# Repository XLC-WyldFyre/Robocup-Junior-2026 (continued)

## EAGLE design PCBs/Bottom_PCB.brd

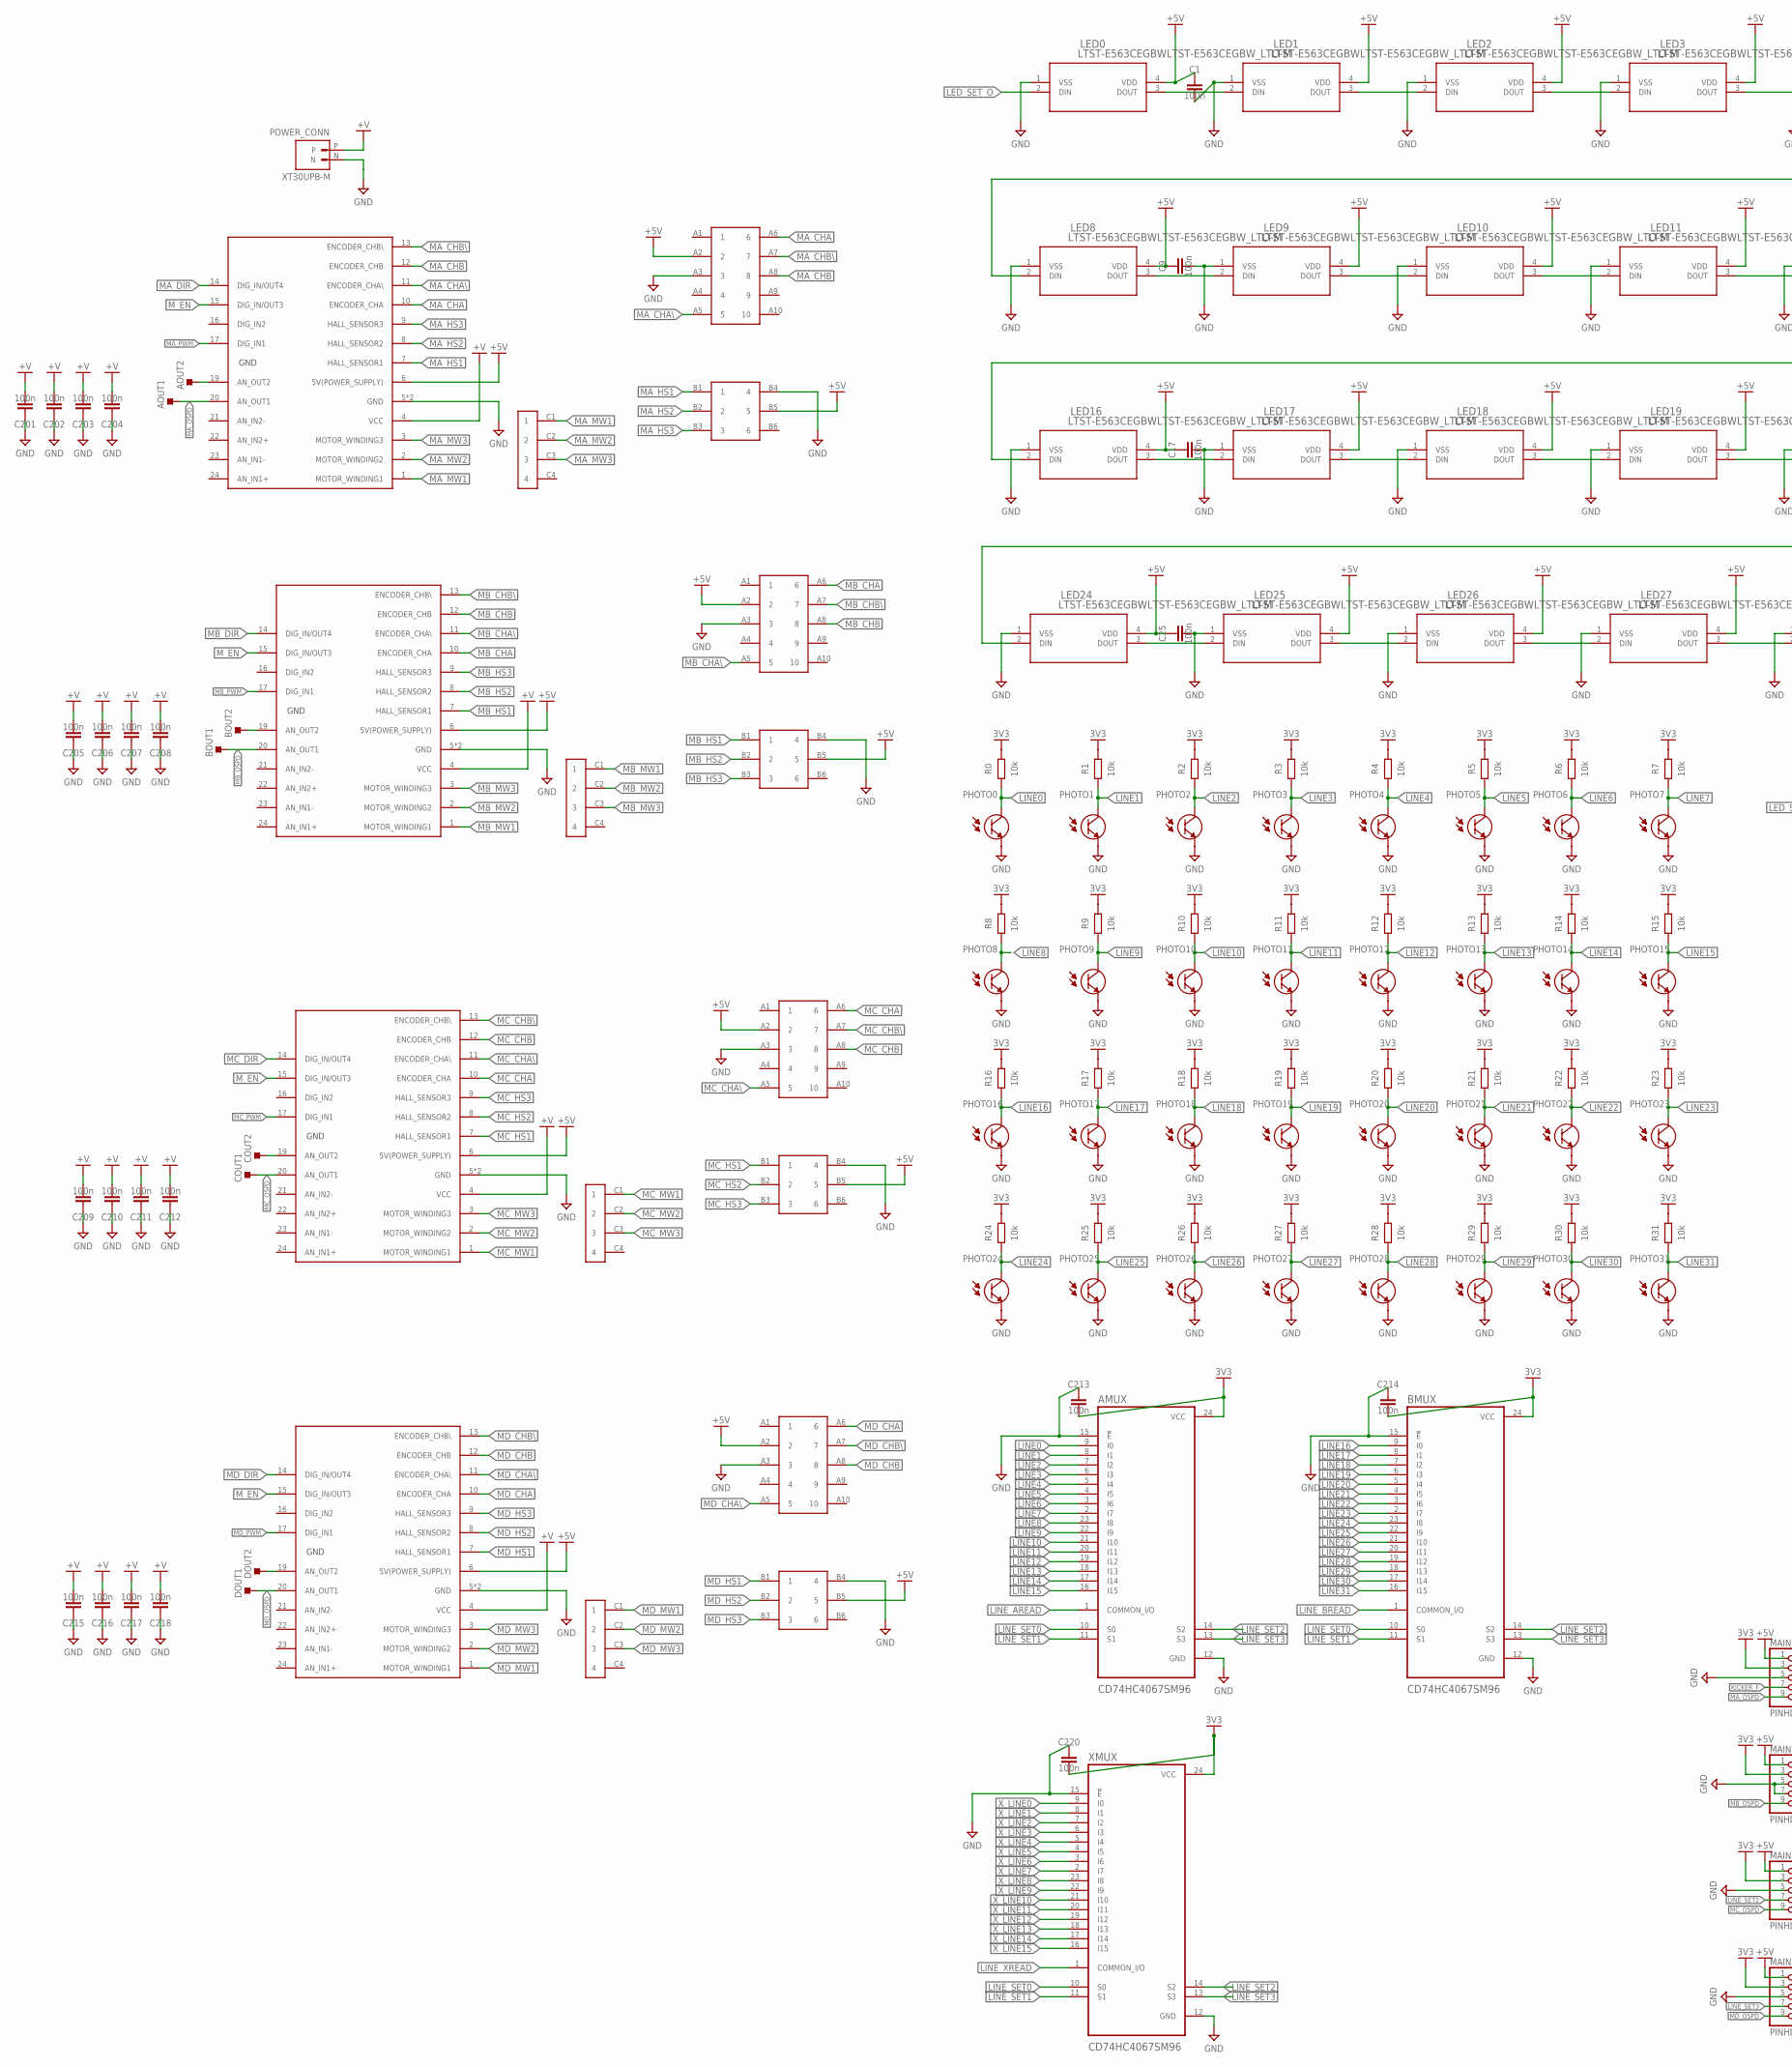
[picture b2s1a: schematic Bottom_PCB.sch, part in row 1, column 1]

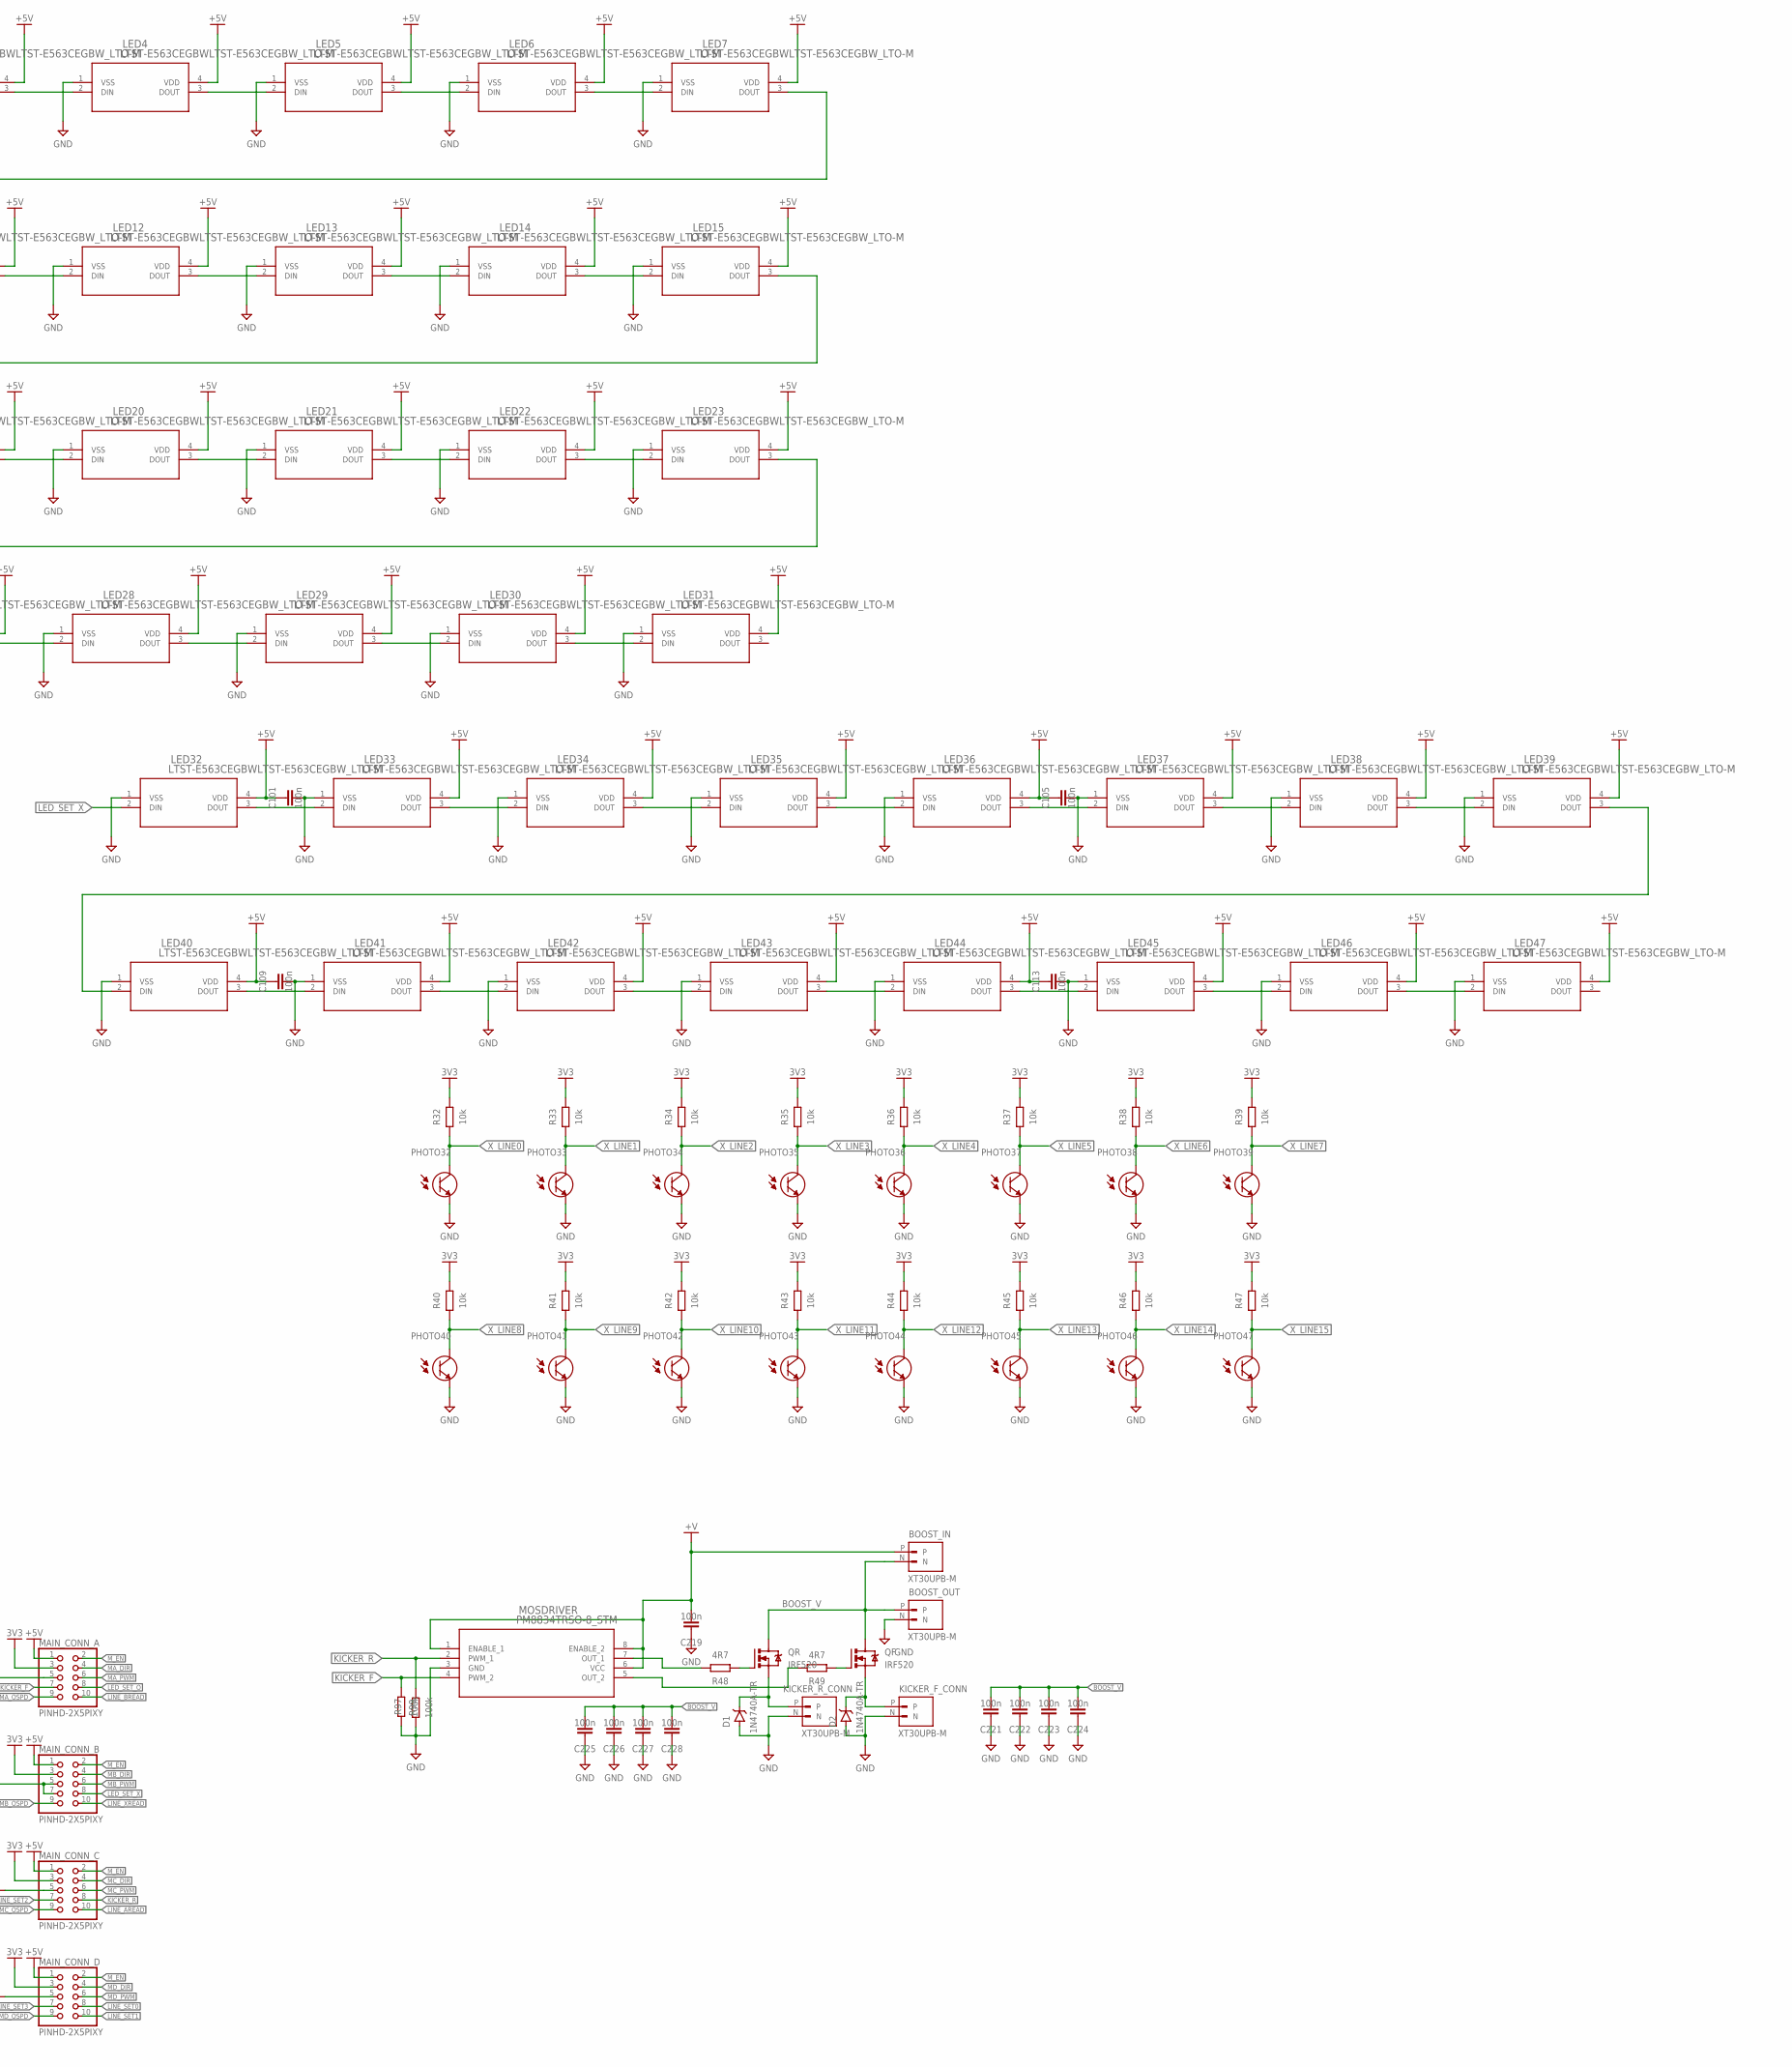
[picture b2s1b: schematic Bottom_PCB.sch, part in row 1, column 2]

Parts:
AENC: PIN2.54-2X5
AHAL: MX-44914-0601
AMD: ESCON24/224/2; ESCON24/2
AMUX: CD74HC4067SM96; SOP65P780X200-24N
AMW: MX5566
AOUT1, AOUT2: TESTPOINT_TPS-PAD-036; TESTPOINT_PAD-036
BENC: PIN2.54-2X5
BHAL: MX-44914-0601
BMD: ESCON24/224/2; ESCON24/2
BMUX: CD74HC4067SM96; SOP65P780X200-24N
BMW: MX5566
BOOST_IN: XT30UPB-M; AMASS_XT30UPB-M
BOOST_OUT: XT30UPB-M; AMASS_XT30UPB-M
BOUT1, BOUT2: TESTPOINT_TPS-PAD-036; TESTPOINT_PAD-036
C1, C9, C17, C25, C101, C105, C109, C113, C201, C202, C203, C204, C205, C206, C207, C208, C209, C210, C211, C212, C213, C214, C215, C216, C217, C218, C219, C220, C221, C222, C223, C224, C225, C226, C227, C228: 100n; CAPC2012X110
CENC: PIN2.54-2X5
CHAL: MX-44914-0601
CMD: ESCON24/224/2; ESCON24/2
CMW: MX5566
COUT1, COUT2: TESTPOINT_TPS-PAD-036; TESTPOINT_PAD-036
D1, D2: 1N4740A-TR; DO-41
DENC: PIN2.54-2X5
DHAL: MX-44914-0601
DMD: ESCON24/224/2; ESCON24/2
DMW: MX5566
DOUT1, DOUT2: TESTPOINT_TPS-PAD-036; TESTPOINT_PAD-036
KICKER_F_CONN: XT30UPB-M; AMASS_XT30UPB-M
KICKER_R_CONN: XT30UPB-M; AMASS_XT30UPB-M
LED0, LED1, LED2, LED3, LED4, LED5, LED6, LED7, LED8, LED9, LED10, LED11, LED12, LED13, LED14, LED15, LED16, LED17, LED18, LED19, LED20, LED21, LED22, LED23, LED24, LED25, LED26, LED27, LED28, LED29, LED30, LED31, LED32, LED33, LED34, LED35, LED36, LED37, LED38, LED39, LED40, LED41, LED42, LED43, LED44, LED45, LED46, LED47: LTST-E563CEGBWLTST-E563CEGBW_LTO-M; LTST-E563CEGBW_LTO-M
MAIN_CONN_A: PINHD-2X5PIXY; 2X05
MAIN_CONN_B: PINHD-2X5PIXY; 2X05
MAIN_CONN_C: PINHD-2X5PIXY; 2X05
MAIN_CONN_D: PINHD-2X5PIXY; 2X05
MOSDRIVER: PM8834TRSO-8_STM; SO-8_STM
PHOTO0, PHOTO1, PHOTO2, PHOTO3, PHOTO4, PHOTO5, PHOTO6, PHOTO7, PHOTO8, PHOTO9, PHOTO10, PHOTO11, PHOTO12, PHOTO13, PHOTO14, PHOTO15, PHOTO16, PHOTO17, PHOTO18, PHOTO19, PHOTO20, PHOTO21, PHOTO22, PHOTO23, PHOTO24, PHOTO25, PHOTO26, PHOTO27, PHOTO28, PHOTO29, PHOTO30, PHOTO31, PHOTO32, PHOTO33, PHOTO34, PHOTO35, PHOTO36, PHOTO37, PHOTO38, PHOTO39, PHOTO40, PHOTO41, PHOTO42, PHOTO43, PHOTO44, PHOTO45, PHOTO46, PHOTO47: RPM-075PTT86TRANS_RPM-075P_ROM; TRANS_RPM-075P_ROM
POWER_CONN: XT30UPB-M; AMASS_XT30UPB-M
QF: IRF520; TO220BV
QR: IRF520; TO220BV
R0, R1, R2, R3, R4, R5, R6, R7, R8, R9, R10, R11, R12, R13, R14, R15, R16, R17, R18, R19, R20, R21, R22, R23, R24, R25, R26, R27, R28, R29, R30, R31, R32, R33, R34, R35, R36, R37, R38, R39, R40, R41, R42, R43, R44, R45, R46, R47: 10k; RESC2012X65
R48, R49: 4R7; RESC2012X65
R97, R98: 100k; RESC2012X65
XMUX: CD74HC4067SM96; SOP65P780X200-24N

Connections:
3V3: AMUX.24 (VCC), BMUX.24 (VCC), C213.2, C214.2, C220.2, MAIN_CONN_A.3, MAIN_CONN_B.3, MAIN_CONN_C.3, MAIN_CONN_D.3, R0.2, R1.2, R2.2, R3.2, R4.2, R5.2, R6.2, R7.2, R8.2, R9.2, R10.2, R11.2, R12.2, R13.2, R14.2, R15.2, R16.2, R17.2, R18.2, R19.2, R20.2, R21.2, R22.2, R23.2, R24.2, R25.2, R26.2, R27.2, R28.2, R29.2, R30.2, R31.2, R32.2, R33.2, R34.2, R35.2, R36.2, R37.2, R38.2, R39.2, R40.2, R41.2, R42.2, R43.2, R44.2, R45.2, R46.2, R47.2, XMUX.24 (VCC)
+5V: AENC.A2 (2), AHAL.B5 (5), AMD.6 (5V(POWER_SUPPLY)), BENC.A2 (2), BHAL.B5 (5), BMD.6 (5V(POWER_SUPPLY)), C1.1, C9.1, C17.1, C25.1, C101.1, C105.1, C109.1, C113.1, CENC.A2 (2), CHAL.B5 (5), CMD.6 (5V(POWER_SUPPLY)), DENC.A2 (2), DHAL.B5 (5), DMD.6 (5V(POWER_SUPPLY)), LED0.4 (VDD), LED1.4 (VDD), LED2.4 (VDD), LED3.4 (VDD), LED4.4 (VDD), LED5.4 (VDD), LED6.4 (VDD), LED7.4 (VDD), LED8.4 (VDD), LED9.4 (VDD), LED10.4 (VDD), LED11.4 (VDD), LED12.4 (VDD), LED13.4 (VDD), LED14.4 (VDD), LED15.4 (VDD), LED16.4 (VDD), LED17.4 (VDD), LED18.4 (VDD), LED19.4 (VDD), LED20.4 (VDD), LED21.4 (VDD), LED22.4 (VDD), LED23.4 (VDD), LED24.4 (VDD), LED25.4 (VDD), LED26.4 (VDD), LED27.4 (VDD), LED28.4 (VDD), LED29.4 (VDD), LED30.4 (VDD), LED31.4 (VDD), LED32.4 (VDD), LED33.4 (VDD), LED34.4 (VDD), LED35.4 (VDD), LED36.4 (VDD), LED37.4 (VDD), LED38.4 (VDD), LED39.4 (VDD), LED40.4 (VDD), LED41.4 (VDD), LED42.4 (VDD), LED43.4 (VDD), LED44.4 (VDD), LED45.4 (VDD), LED46.4 (VDD), LED47.4 (VDD), MAIN_CONN_A.1, MAIN_CONN_B.1, MAIN_CONN_C.1, MAIN_CONN_D.1
+V: AMD.4 (VCC), BMD.4 (VCC), BOOST_IN.P, C201.2, C202.2, C203.2, C204.2, C205.2, C206.2, C207.2, C208.2, C209.2, C210.2, C211.2, C212.2, C215.2, C216.2, C217.2, C218.2, C219.2, CMD.4 (VCC), DMD.4 (VCC), MOSDRIVER.1 (ENABLE_1), MOSDRIVER.6 (VCC), MOSDRIVER.8 (ENABLE_2), POWER_CONN.P
BOOST_V: BOOST_IN.N, BOOST_OUT.P, C221.2, C222.2, C223.2, C224.2, C225.2, C226.2, C227.2, C228.2, QF.D, QR.D
GND: AENC.A3 (3), AHAL.B4 (4), AMD.5 (GND), AMD.18 (GND), AMUX.12 (GND), AMUX.15 (!E), BENC.A3 (3), BHAL.B4 (4), BMD.5 (GND), BMD.18 (GND), BMUX.12 (GND), BMUX.15 (!E), BOOST_OUT.N, C1.2, C9.2, C17.2, C25.2, C101.2, C105.2, C109.2, C113.2, C201.1, C202.1, C203.1, C204.1, C205.1, C206.1, C207.1, C208.1, C209.1, C210.1, C211.1, C212.1, C213.1, C214.1, C215.1, C216.1, C217.1, C218.1, C219.1, C220.1, C221.1, C222.1, C223.1, C224.1, C225.1, C226.1, C227.1, C228.1, CENC.A3 (3), CHAL.B4 (4), CMD.5 (GND), CMD.18 (GND), D1.A, D2.A, DENC.A3 (3), DHAL.B4 (4), DMD.5 (GND), DMD.18 (GND), KICKER_F_CONN.N, KICKER_R_CONN.N, LED0.1 (VSS), LED1.1 (VSS), LED2.1 (VSS), LED3.1 (VSS), LED4.1 (VSS), LED5.1 (VSS), LED6.1 (VSS), LED7.1 (VSS), LED8.1 (VSS), LED9.1 (VSS), LED10.1 (VSS), LED11.1 (VSS), LED12.1 (VSS), LED13.1 (VSS), LED14.1 (VSS), LED15.1 (VSS), LED16.1 (VSS), LED17.1 (VSS), LED18.1 (VSS), LED19.1 (VSS), LED20.1 (VSS), LED21.1 (VSS), LED22.1 (VSS), LED23.1 (VSS), LED24.1 (VSS), LED25.1 (VSS), LED26.1 (VSS), LED27.1 (VSS), LED28.1 (VSS), LED29.1 (VSS), LED30.1 (VSS), LED31.1 (VSS), LED32.1 (VSS), LED33.1 (VSS), LED34.1 (VSS), LED35.1 (VSS), LED36.1 (VSS), LED37.1 (VSS), LED38.1 (VSS), LED39.1 (VSS), LED40.1 (VSS), LED41.1 (VSS), LED42.1 (VSS), LED43.1 (VSS), LED44.1 (VSS), LED45.1 (VSS), LED46.1 (VSS), LED47.1 (VSS), MAIN_CONN_A.5, MAIN_CONN_B.5, MAIN_CONN_B.7, MAIN_CONN_C.5, MAIN_CONN_D.5, MOSDRIVER.3 (GND), PHOTO0.1, PHOTO1.1, PHOTO2.1, PHOTO3.1, PHOTO4.1, PHOTO5.1, PHOTO6.1, PHOTO7.1, PHOTO8.1, PHOTO9.1, PHOTO10.1, PHOTO11.1, PHOTO12.1, PHOTO13.1, PHOTO14.1, PHOTO15.1, PHOTO16.1, PHOTO17.1, PHOTO18.1, PHOTO19.1, PHOTO20.1, PHOTO21.1, PHOTO22.1, PHOTO23.1, PHOTO24.1, PHOTO25.1, PHOTO26.1, PHOTO27.1, PHOTO28.1, PHOTO29.1, PHOTO30.1, PHOTO31.1, PHOTO32.1, PHOTO33.1, PHOTO34.1, PHOTO35.1, PHOTO36.1, PHOTO37.1, PHOTO38.1, PHOTO39.1, PHOTO40.1, PHOTO41.1, PHOTO42.1, PHOTO43.1, PHOTO44.1, PHOTO45.1, PHOTO46.1, PHOTO47.1, POWER_CONN.N, R97.1, R98.1, XMUX.12 (GND), XMUX.15 (!E)
KICKER_F: MAIN_CONN_A.7, MOSDRIVER.4 (PWM_2), R97.2
KICKER_R: MAIN_CONN_C.8, MOSDRIVER.2 (PWM_1), R98.2
LED_SET_O: LED0.2 (DIN), MAIN_CONN_A.8
LED_SET_X: LED32.2 (DIN), MAIN_CONN_B.8
LINE0: AMUX.9 (I0), PHOTO0.2, R0.1
LINE1: AMUX.8 (I1), PHOTO1.2, R1.1
LINE2: AMUX.7 (I2), PHOTO2.2, R2.1
LINE3: AMUX.6 (I3), PHOTO3.2, R3.1
LINE4: AMUX.5 (I4), PHOTO4.2, R4.1
LINE5: AMUX.4 (I5), PHOTO5.2, R5.1
LINE6: AMUX.3 (I6), PHOTO6.2, R6.1
LINE7: AMUX.2 (I7), PHOTO7.2, R7.1
LINE8: AMUX.23 (I8), PHOTO8.2, R8.1
LINE9: AMUX.22 (I9), PHOTO9.2, R9.1
LINE10: AMUX.21 (I10), PHOTO10.2, R10.1
LINE11: AMUX.20 (I11), PHOTO11.2, R11.1
LINE12: AMUX.19 (I12), PHOTO12.2, R12.1
LINE13: AMUX.18 (I13), PHOTO13.2, R13.1
LINE14: AMUX.17 (I14), PHOTO14.2, R14.1
LINE15: AMUX.16 (I15), PHOTO15.2, R15.1
LINE16: BMUX.9 (I0), PHOTO16.2, R16.1
LINE17: BMUX.8 (I1), PHOTO17.2, R17.1
LINE18: BMUX.7 (I2), PHOTO18.2, R18.1
LINE19: BMUX.6 (I3), PHOTO19.2, R19.1
LINE20: BMUX.5 (I4), PHOTO20.2, R20.1
LINE21: BMUX.4 (I5), PHOTO21.2, R21.1
LINE22: BMUX.3 (I6), PHOTO22.2, R22.1
LINE23: BMUX.2 (I7), PHOTO23.2, R23.1
LINE24: BMUX.23 (I8), PHOTO24.2, R24.1
LINE25: BMUX.22 (I9), PHOTO25.2, R25.1
LINE26: BMUX.21 (I10), PHOTO26.2, R26.1
LINE27: BMUX.20 (I11), PHOTO27.2, R27.1
LINE28: BMUX.19 (I12), PHOTO28.2, R28.1
LINE29: BMUX.18 (I13), PHOTO29.2, R29.1
LINE30: BMUX.17 (I14), PHOTO30.2, R30.1
LINE31: BMUX.16 (I15), PHOTO31.2, R31.1
LINE_AREAD: AMUX.1 (COMMON_I/O), MAIN_CONN_C.10
LINE_BREAD: BMUX.1 (COMMON_I/O), MAIN_CONN_A.10
LINE_SET0: AMUX.10 (S0), BMUX.10 (S0), MAIN_CONN_D.8, XMUX.10 (S0)
LINE_SET1: AMUX.11 (S1), BMUX.11 (S1), MAIN_CONN_D.10, XMUX.11 (S1)
LINE_SET2: AMUX.14 (S2), BMUX.14 (S2), MAIN_CONN_C.7, XMUX.14 (S2)
LINE_SET3: AMUX.13 (S3), BMUX.13 (S3), MAIN_CONN_D.7, XMUX.13 (S3)
LINE_XREAD: MAIN_CONN_B.10, XMUX.1 (COMMON_I/O)
MA_CHA: AENC.A6 (6), AMD.10 (ENCODER_CHA)
MA_CHA\\: AENC.A5 (5), AMD.11 (ENCODER_CHA\\)
MA_CHB: AENC.A8 (8), AMD.12 (ENCODER_CHB)
MA_CHB\\: AENC.A7 (7), AMD.13 (ENCODER_CHB\\)
MA_DIR: AMD.14 (DIG_IN/OUT4), MAIN_CONN_A.4
MA_HS1: AHAL.B1 (1), AMD.7 (HALL_SENSOR1)
MA_HS2: AHAL.B2 (2), AMD.8 (HALL_SENSOR2)
MA_HS3: AHAL.B3 (3), AMD.9 (HALL_SENSOR3)
MA_MW1: AMD.1 (MOTOR_WINDING1), AMW.C1 (1)
MA_MW2: AMD.2 (MOTOR_WINDING2), AMW.C2 (2)
MA_MW3: AMD.3 (MOTOR_WINDING3), AMW.C3 (3)
MA_OSPD: AMD.20 (AN_OUT1), AOUT1.1, MAIN_CONN_A.9
MA_PWM: AMD.17 (DIG_IN1), MAIN_CONN_A.6
MB_CHA: BENC.A6 (6), BMD.10 (ENCODER_CHA)
MB_CHA\\: BENC.A5 (5), BMD.11 (ENCODER_CHA\\)
MB_CHB: BENC.A8 (8), BMD.12 (ENCODER_CHB)
MB_CHB\\: BENC.A7 (7), BMD.13 (ENCODER_CHB\\)
MB_DIR: BMD.14 (DIG_IN/OUT4), MAIN_CONN_B.4
MB_HS1: BHAL.B1 (1), BMD.7 (HALL_SENSOR1)
MB_HS2: BHAL.B2 (2), BMD.8 (HALL_SENSOR2)
MB_HS3: BHAL.B3 (3), BMD.9 (HALL_SENSOR3)
MB_MW1: BMD.1 (MOTOR_WINDING1), BMW.C1 (1)
MB_MW2: BMD.2 (MOTOR_WINDING2), BMW.C2 (2)
MB_MW3: BMD.3 (MOTOR_WINDING3), BMW.C3 (3)
MB_OSPD: BMD.20 (AN_OUT1), BOUT1.1, MAIN_CONN_B.9
MB_PWM: BMD.17 (DIG_IN1), MAIN_CONN_B.6
MC_CHA: CENC.A6 (6), CMD.10 (ENCODER_CHA)
MC_CHA\\: CENC.A5 (5), CMD.11 (ENCODER_CHA\\)
MC_CHB: CENC.A8 (8), CMD.12 (ENCODER_CHB)
MC_CHB\\: CENC.A7 (7), CMD.13 (ENCODER_CHB\\)
MC_DIR: CMD.14 (DIG_IN/OUT4), MAIN_CONN_C.4
MC_HS1: CHAL.B1 (1), CMD.7 (HALL_SENSOR1)
MC_HS2: CHAL.B2 (2), CMD.8 (HALL_SENSOR2)
MC_HS3: CHAL.B3 (3), CMD.9 (HALL_SENSOR3)
MC_MW1: CMD.1 (MOTOR_WINDING1), CMW.C1 (1)
MC_MW2: CMD.2 (MOTOR_WINDING2), CMW.C2 (2)
MC_MW3: CMD.3 (MOTOR_WINDING3), CMW.C3 (3)
MC_OSPD: CMD.20 (AN_OUT1), COUT1.1, MAIN_CONN_C.9
MC_PWM: CMD.17 (DIG_IN1), MAIN_CONN_C.6
MD_CHA: DENC.A6 (6), DMD.10 (ENCODER_CHA)
MD_CHA\\: DENC.A5 (5), DMD.11 (ENCODER_CHA\\)
MD_CHB: DENC.A8 (8), DMD.12 (ENCODER_CHB)
MD_CHB\\: DENC.A7 (7), DMD.13 (ENCODER_CHB\\)
MD_DIR: DMD.14 (DIG_IN/OUT4), MAIN_CONN_D.4
MD_HS1: DHAL.B1 (1), DMD.7 (HALL_SENSOR1)
MD_HS2: DHAL.B2 (2), DMD.8 (HALL_SENSOR2)
MD_HS3: DHAL.B3 (3), DMD.9 (HALL_SENSOR3)
MD_MW1: DMD.1 (MOTOR_WINDING1), DMW.C1 (1)
MD_MW2: DMD.2 (MOTOR_WINDING2), DMW.C2 (2)
MD_MW3: DMD.3 (MOTOR_WINDING3), DMW.C3 (3)
MD_OSPD: DMD.20 (AN_OUT1), DOUT1.1, MAIN_CONN_D.9
MD_PWM: DMD.17 (DIG_IN1), MAIN_CONN_D.6
M_EN: AMD.15 (DIG_IN/OUT3), BMD.15 (DIG_IN/OUT3), CMD.15 (DIG_IN/OUT3), DMD.15 (DIG_IN/OUT3), MAIN_CONN_A.2, MAIN_CONN_B.2, MAIN_CONN_C.2, MAIN_CONN_D.2
unnamed: LED8.3 (DOUT), LED9.2 (DIN)
unnamed: LED10.3 (DOUT), LED11.2 (DIN)
unnamed: LED11.3 (DOUT), LED12.2 (DIN)
unnamed: LED9.3 (DOUT), LED10.2 (DIN)
unnamed: LED12.3 (DOUT), LED13.2 (DIN)
unnamed: LED13.3 (DOUT), LED14.2 (DIN)
unnamed: LED14.3 (DOUT), LED15.2 (DIN)
unnamed: LED15.3 (DOUT), LED16.2 (DIN)
unnamed: LED16.3 (DOUT), LED17.2 (DIN)
unnamed: LED17.3 (DOUT), LED18.2 (DIN)
unnamed: LED18.3 (DOUT), LED19.2 (DIN)
unnamed: LED19.3 (DOUT), LED20.2 (DIN)
unnamed: LED20.3 (DOUT), LED21.2 (DIN)
unnamed: LED21.3 (DOUT), LED22.2 (DIN)
unnamed: LED22.3 (DOUT), LED23.2 (DIN)
unnamed: LED23.3 (DOUT), LED24.2 (DIN)
unnamed: LED24.3 (DOUT), LED25.2 (DIN)
unnamed: LED25.3 (DOUT), LED26.2 (DIN)
unnamed: LED26.3 (DOUT), LED27.2 (DIN)
unnamed: LED27.3 (DOUT), LED28.2 (DIN)
unnamed: LED28.3 (DOUT), LED29.2 (DIN)
unnamed: LED29.3 (DOUT), LED30.2 (DIN)
unnamed: LED30.3 (DOUT), LED31.2 (DIN)
unnamed: LED0.3 (DOUT), LED1.2 (DIN)
unnamed: LED1.3 (DOUT), LED2.2 (DIN)
unnamed: LED2.3 (DOUT), LED3.2 (DIN)
unnamed: LED3.3 (DOUT), LED4.2 (DIN)
unnamed: LED4.3 (DOUT), LED5.2 (DIN)
unnamed: LED5.3 (DOUT), LED6.2 (DIN)
unnamed: LED6.3 (DOUT), LED7.2 (DIN)
unnamed: LED7.3 (DOUT), LED8.2 (DIN)
unnamed: D1.C, KICKER_R_CONN.P, QR.S
unnamed: D2.C, KICKER_F_CONN.P, QF.S
unnamed: QF.G, R49.1
unnamed: LED40.3 (DOUT), LED41.2 (DIN)
unnamed: LED41.3 (DOUT), LED42.2 (DIN)
unnamed: LED42.3 (DOUT), LED43.2 (DIN)
unnamed: LED43.3 (DOUT), LED44.2 (DIN)
unnamed: LED44.3 (DOUT), LED45.2 (DIN)
unnamed: LED45.3 (DOUT), LED46.2 (DIN)
unnamed: LED46.3 (DOUT), LED47.2 (DIN)
unnamed: MOSDRIVER.7 (OUT_1), R48.2
unnamed: LED32.3 (DOUT), LED33.2 (DIN)
unnamed: LED33.3 (DOUT), LED34.2 (DIN)
unnamed: LED34.3 (DOUT), LED35.2 (DIN)
unnamed: LED35.3 (DOUT), LED36.2 (DIN)
unnamed: LED36.3 (DOUT), LED37.2 (DIN)
unnamed: LED37.3 (DOUT), LED38.2 (DIN)
unnamed: LED38.3 (DOUT), LED39.2 (DIN)
unnamed: LED39.3 (DOUT), LED40.2 (DIN)
unnamed: MOSDRIVER.5 (OUT_2), R49.2
unnamed: AMD.19 (AN_OUT2), AOUT2.1
unnamed: QR.G, R48.1
unnamed: BMD.19 (AN_OUT2), BOUT2.1
unnamed: CMD.19 (AN_OUT2), COUT2.1
unnamed: DMD.19 (AN_OUT2), DOUT2.1
X_LINE0: PHOTO32.2, R32.1, XMUX.9 (I0)
X_LINE1: PHOTO33.2, R33.1, XMUX.8 (I1)
X_LINE2: PHOTO34.2, R34.1, XMUX.7 (I2)
X_LINE3: PHOTO35.2, R35.1, XMUX.6 (I3)
X_LINE4: PHOTO36.2, R36.1, XMUX.5 (I4)
X_LINE5: PHOTO37.2, R37.1, XMUX.4 (I5)
X_LINE6: PHOTO38.2, R38.1, XMUX.3 (I6)
X_LINE7: PHOTO39.2, R39.1, XMUX.2 (I7)
X_LINE8: PHOTO40.2, R40.1, XMUX.23 (I8)
X_LINE9: PHOTO41.2, R41.1, XMUX.22 (I9)
X_LINE10: PHOTO42.2, R42.1, XMUX.21 (I10)
X_LINE11: PHOTO43.2, R43.1, XMUX.20 (I11)
X_LINE12: PHOTO44.2, R44.1, XMUX.19 (I12)
X_LINE13: PHOTO45.2, R45.1, XMUX.18 (I13)
X_LINE14: PHOTO46.2, R46.1, XMUX.17 (I14)
X_LINE15: PHOTO47.2, R47.1, XMUX.16 (I15)

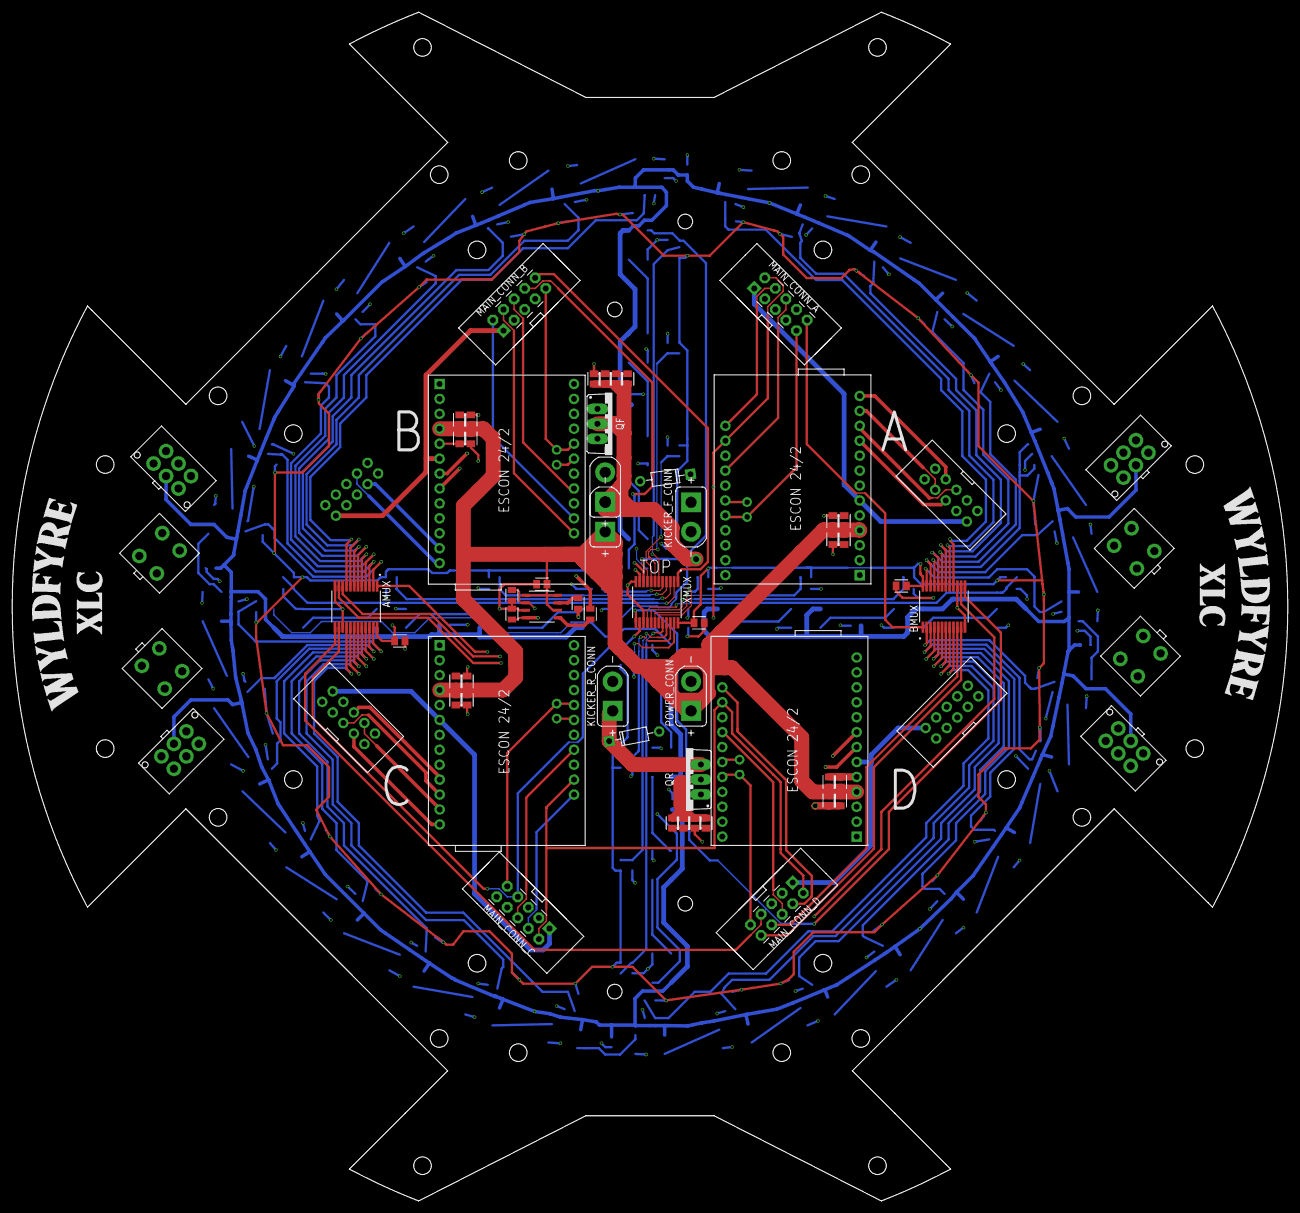
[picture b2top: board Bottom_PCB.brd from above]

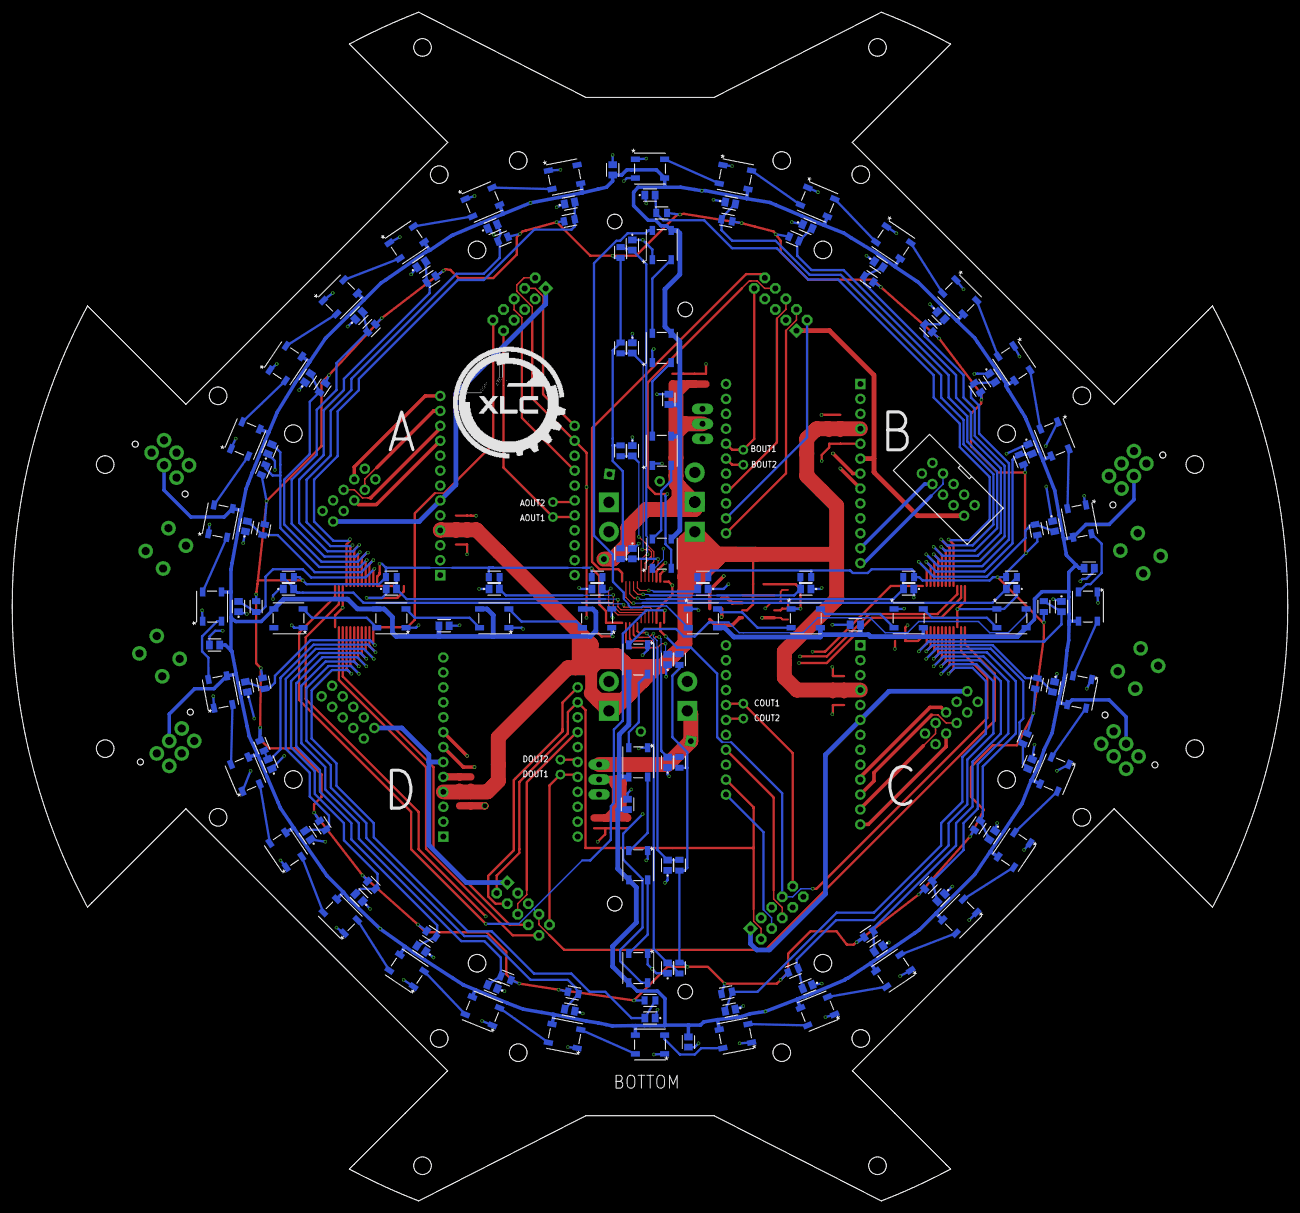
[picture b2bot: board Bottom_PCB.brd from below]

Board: 4 copper layers, 217.0 x 202.2 mm, 225 parts (161 on the bottom side), 173 nets.

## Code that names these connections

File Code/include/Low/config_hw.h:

#pragma once
#include "driver/gpio.h"


namespace HW {

    namespace Comms {
        constexpr uint8_t SOCCER_PEER_MAC_A [6] = {0x14, 0xC1, 0x9F, 0x38, 0xB5, 0xB0}; //scorpion
        constexpr uint8_t SOCCER_PEER_MAC_B [6] = {0x10, 0x51, 0xDB, 0x50, 0x24, 0x0C}; //crocodile

        constexpr uint8_t CONTROLLER_PEER_MAC_A [6] = {0xB0, 0xA7, 0x32, 0x28, 0x60, 0x00};
        constexpr uint8_t CONTROLLER_PEER_MAC_B [6] = {0xB0, 0xA7, 0x32, 0x28, 0x60, 0x00};

        constexpr int ESPNOW_CHANNEL = 1;
    }

    namespace Controller { 
        constexpr uint8_t I2C_ADDR = 0x42;

        constexpr float TRIGG_CONST = 1.0f/255.0f;
        constexpr float DEAD_CONST = 0.1f;
        constexpr float STICK_CONST = 1.0f/512.0f;
    }

    namespace MotorCfg {
        //MOTORS
        constexpr gpio_num_t EnPin = GPIO_NUM_38;
        constexpr gpio_num_t A_DirPin = GPIO_NUM_42;
        constexpr gpio_num_t A_PwmPin = GPIO_NUM_41;
        constexpr gpio_num_t B_DirPin = GPIO_NUM_48;
        constexpr gpio_num_t B_PwmPin = GPIO_NUM_47;
        constexpr gpio_num_t C_DirPin = GPIO_NUM_14;
        constexpr gpio_num_t C_PwmPin = GPIO_NUM_13;
        constexpr gpio_num_t D_DirPin = GPIO_NUM_12;
        constexpr gpio_num_t D_PwmPin = GPIO_NUM_11;

    }

    namespace PWMCfg {
        constexpr int PWM_FREQ = 1000; //Hz
        constexpr int PWM_RES = 12; //bits
    }
    
    namespace KickerDrbCfg {
        //DRIBLER
        constexpr gpio_num_t DRB_DirPin = GPIO_NUM_2;
        constexpr gpio_num_t DRB_PwmPin = GPIO_NUM_10;
        //KICKER
        constexpr gpio_num_t Kicker_F_Pin = GPIO_NUM_7;
        constexpr gpio_num_t Kicker_R_Pin = GPIO_NUM_21;
    }

    namespace DisplayCfg {
        constexpr int width = 128;
        constexpr int height = 64;
        constexpr int ADRR = 0x3C;
        constexpr int rotation = 2; 
    }

    namespace MotionSenseCfg{
        //MOTORS SENSE
        
        // constexpr gpio_num_t DRBFR_Spd_Pin = GPIO_NUM_1;
        constexpr gpio_num_t A_Spd_Pin = GPIO_NUM_15;
        constexpr gpio_num_t B_Spd_Pin = GPIO_NUM_16;
        constexpr gpio_num_t C_Spd_Pin = GPIO_NUM_17;
        constexpr gpio_num_t D_Spd_Pin = GPIO_NUM_18;
        
        
        constexpr uint16_t ADC_maxVal = 4095;

        //SWITCHES
        constexpr gpio_num_t DRB_SW_F_Pin = GPIO_NUM_40;
        constexpr gpio_num_t DRB_SW_R_Pin = GPIO_NUM_39;

    }



    namespace GenericCfg {

            constexpr int HW_BTN_DEBOUNCE_MS = 20;
            constexpr int HW_BTN_LONGPRESS_MS = 500;
        
            constexpr int SW_BTN_DEBOUNCE_MS = 20;
            constexpr int SW_BTN_LONGPRESS_MS = 500;

            //BUTTONS
            constexpr gpio_num_t BTN_inc_Pin = GPIO_NUM_20;
            constexpr gpio_num_t BTN_dec_Pin = GPIO_NUM_19;
            //BUKAJ MODUL
            constexpr gpio_num_t BukajModule_Pin = GPIO_NUM_35;
            //I2C
            constexpr int I2C_SDA_Pin = 8;
            constexpr int I2C_SCL_Pin = 9;
            // constexpr int I2C_SPEED = 1000000UL;
            
            constexpr int I2C_SPEED = 400000UL;
            
            constexpr int SERIAL_SPEED = 921600;
    }

    namespace LineCfg{
        //LINE MUX
        constexpr int Line_A_Read_Pin = 4;
        constexpr int Line_B_Read_Pin = 5;
        constexpr int Line_X_Read_Pin = 6;
        constexpr int Line_A_Read_ADC_CH = 3;
        constexpr int Line_B_Read_ADC_CH = 4;
        constexpr int Line_X_Read_ADC_CH = 5;
        constexpr gpio_num_t LineSet0_Pin = GPIO_NUM_0;
        constexpr gpio_num_t LineSet1_Pin = GPIO_NUM_45;
        constexpr gpio_num_t LineSet2_Pin = GPIO_NUM_46;
        constexpr gpio_num_t LineSet3_Pin = GPIO_NUM_3;
        
        //line treshold sense
        constexpr int line_analog_treshold = 250;
        constexpr float line_depth_O_Val = 0.05f;
        //                                      45%   30%   15%    10%
        constexpr float line_depth_XArr[4] = {0.45f, 0.3f, 0.15f, 0.1f}; //percentage of robot on line

    }

    namespace LEDsCfg {
        constexpr int LEDSetO_Pin = 36;
        constexpr int LEDSet_Xdebug_Pin = 37;

        constexpr int LED_O_num = 32;
        constexpr int LED_X_num = 20;
        constexpr uint16_t LED_DEBUG_num = 4;

        constexpr float DEBUG_BRIGHTNESS = 0.01f;
    }

    namespace GyroCfg {
        constexpr int GYRO_ID = 55;
        constexpr int GYRO_ADR = 0x28;
    }


    namespace BallCfg {
        constexpr int IR_ADRR = 0x10;
        constexpr int IR_AngDis_REG = 0x00;
        constexpr int IR_RAW_REG = 0x01;
        constexpr int IR_RAW_COUNT = 13;

        static const float FRONT_OFFSET_DEG = 145.0f;

        static const float NEAR_SENSOR_ANGLE_DEG[12] = {
            0.0f, 30.0f, 60.0f, 90.0f, 120.0f, 150.0f,
            180.0f, 210.0f, 240.0f, 270.0f, 300.0f, 330.0f };

        static const float FAR_SENSOR_ANGLE_DEG[6] = {
            0.0f, 60.0f, 120.0f, 180.0f, 240.0f, 300.0f };

        const float ALPHA_NEAR = 0.15f;   // bolo 0.40
        const float ALPHA_FAR  = 0.08f;   // bolo 0.18
        const float MAX_JUMP_NEAR = 35.0f; // bolo 55
        const float MAX_JUMP_FAR  = 18.0f; // bolo 25

        const int MIN_SUM_NEAR = 20;
        const int MIN_SUM_FAR = 8;
        const float MIN_DIR_NEAR = 0.08f;
        const float MIN_DIR_FAR = 0.05f;

        constexpr int c_ballignoreDistance = 1000;
        constexpr int c_ballEffectiveInputClosest = 2500;
        constexpr int c_ballEffectiveInputFurthes = 2100;
    }

    namespace PixyCfg {
        constexpr int c_pixy_frameWidth = 316;  //camera pixel width
        constexpr int c_pixy_frameHeight = 208; //camera pixel height
        constexpr int c_pixy_objMinHeight = 115; //minimum height of object to be detected
        constexpr float c_pixy_FOV = 60.0f;

        constexpr int c_GoalSigEnemy = 1;   //Signatures from PixyMon 
        constexpr int c_GoalSigOur = 2;

    }

}

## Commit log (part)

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2026-04-30 Create lib
